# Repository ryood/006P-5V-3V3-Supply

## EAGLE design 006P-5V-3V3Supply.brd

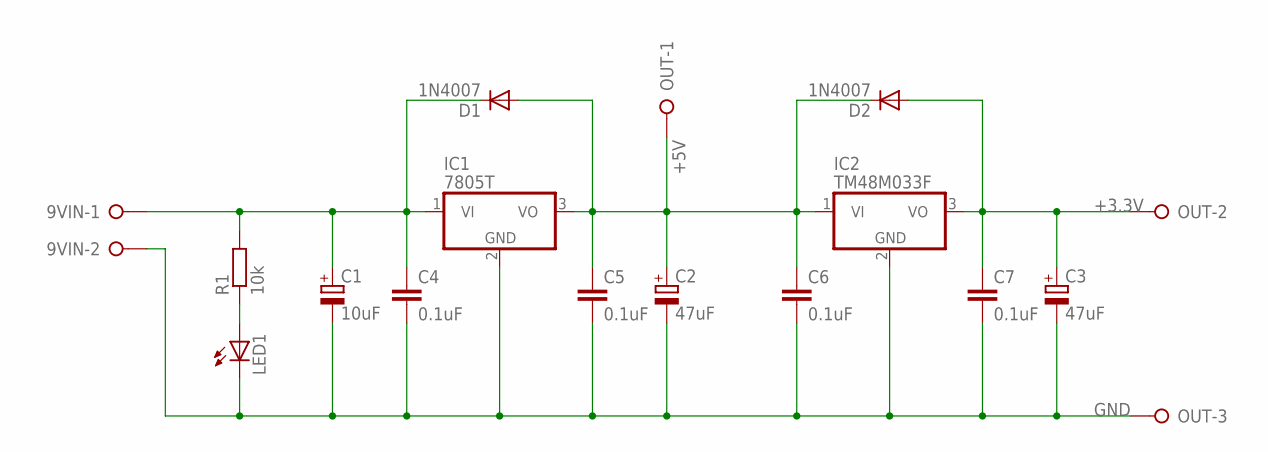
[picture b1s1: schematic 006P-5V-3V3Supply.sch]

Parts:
9VIN: W237-02P; W237-132
C1: 10uF; TT2D4L
C2, C3: 47uF; TT2D5L
C4, C5, C6, C7: 0.1uF; C025-024X044
D1, D2: 1N4007; DO41-10
IC1: 7805T; TO220H
IC2: TM48M033F; TO220V
LED1: LED3MM
OUT: W237-03P; W237-133
R1: 10k; 0207/7

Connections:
+3.3V: C3.+, C7.1, D2.A, IC2.3 (VO), OUT.2
+5V: C2.+, C5.1, C6.1, D1.A, D2.C, IC1.3 (VO), IC2.1 (VI), OUT.1
GND: 9VIN.2, C1.-, C2.-, C3.-, C4.2, C5.2, C6.2, C7.2, IC1.2 (GND), IC2.2 (GND), LED1.K (C), OUT.3
IN9V: 9VIN.1, C1.+, C4.1, D1.C, IC1.1 (VI), R1.2
unnamed: LED1.A, R1.1

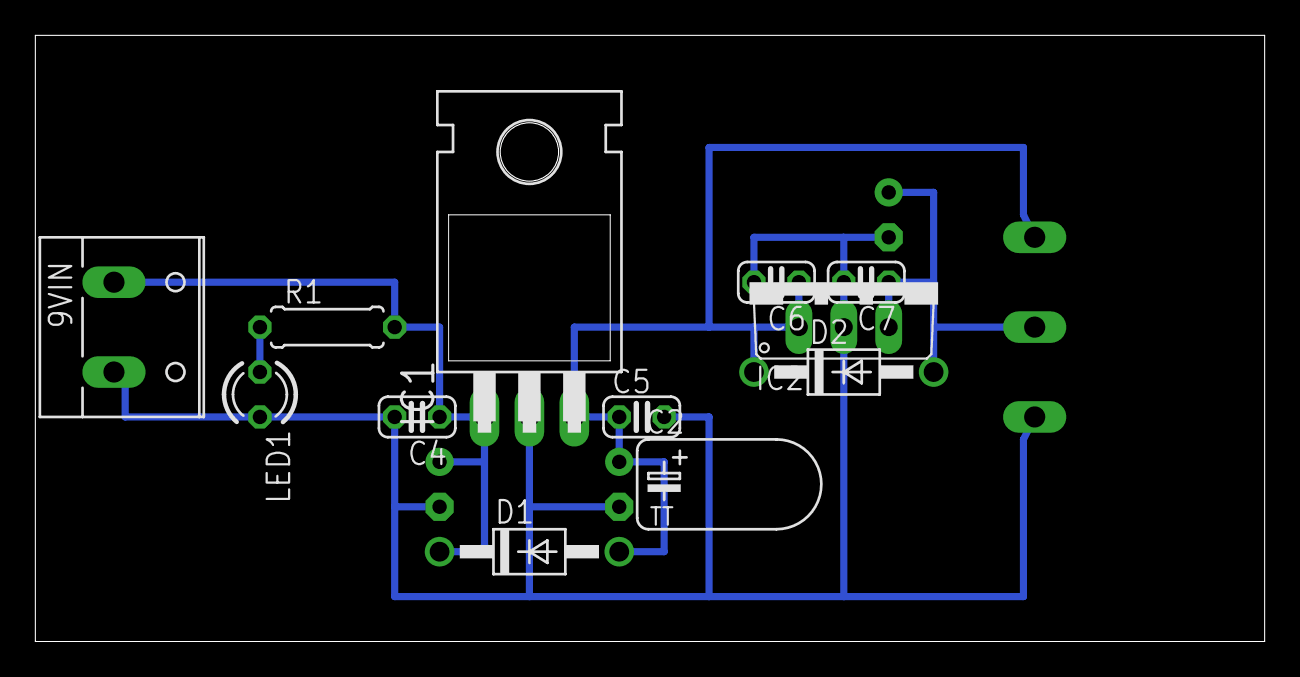
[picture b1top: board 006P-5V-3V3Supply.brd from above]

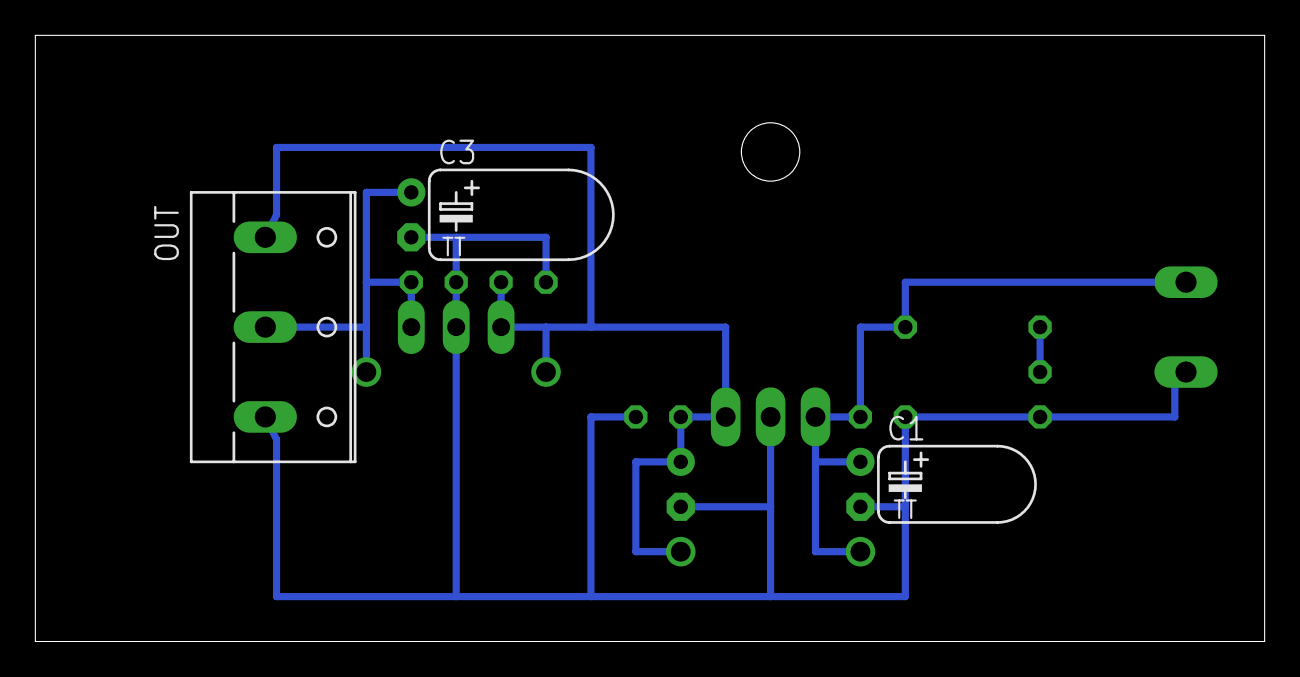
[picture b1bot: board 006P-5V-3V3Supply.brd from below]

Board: 2 copper layers, 69.5 x 34.3 mm, 15 parts (3 on the bottom side), 5 nets.

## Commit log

2015-06-13 回路図、基板図を修正
2015-06-13 3.3V-5V_Supply-ケース内配線.fzz: ケース内配線図を追加
2015-06-13 3.3V-5V_Supply_Case.dwg: ケース加工図を追加
2015-06-13 PNGファイルを追加
